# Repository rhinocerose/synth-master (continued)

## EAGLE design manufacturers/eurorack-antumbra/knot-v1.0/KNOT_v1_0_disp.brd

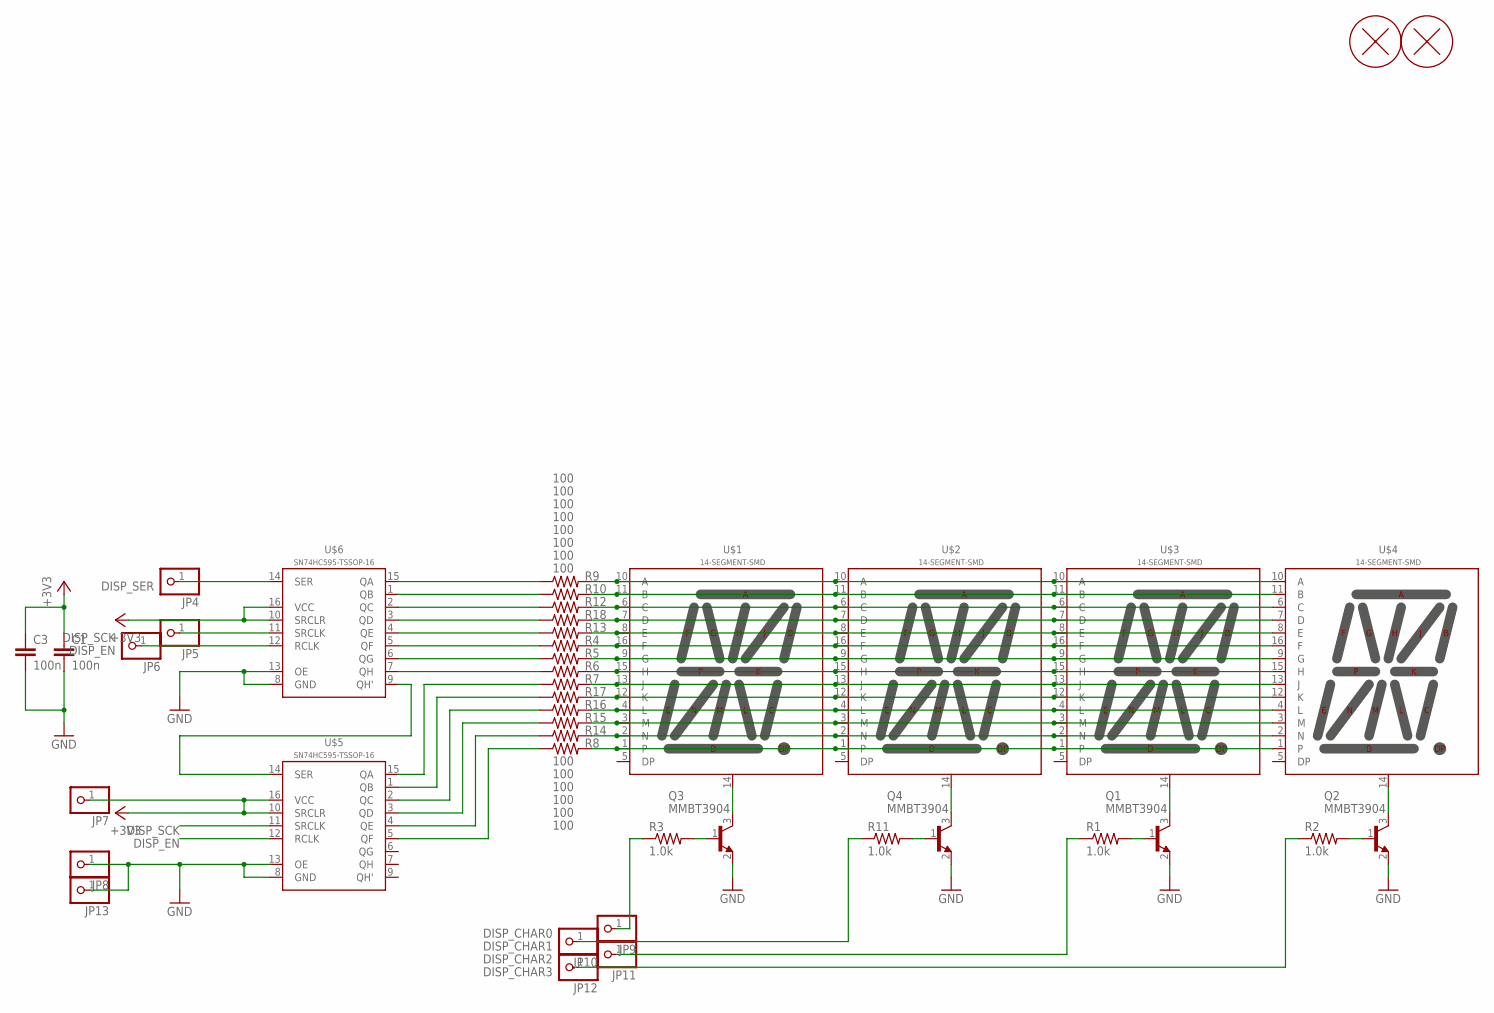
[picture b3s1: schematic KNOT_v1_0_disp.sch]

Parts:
C1, C3: 100n; RESISTOR_0603
H1, H2: PCB_SCREW
JP4, JP5, JP6, JP7, JP8, JP9, JP10, JP11, JP12, JP13: PINHD-1X1; 1X01
Q1, Q2, Q3, Q4: MMBT3904; SOT23
R1, R2, R3, R11: 1.0k; RESISTOR_0603
R4, R5, R6, R7, R8, R9, R10, R12, R13, R14, R15, R16, R17, R18: 100; RESISTOR_0603
U$1, U$2, U$3, U$4: 14-SEGMENT-SMD; 14-SEGMENT-0.4"-SMD
U$5, U$6: SN74HC595-TSSOP-16; TSSOP-16

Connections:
+3V3: C1.1, C3.1, JP7.1, U$5.10 (SRCLR), U$5.16 (VCC), U$6.10 (SRCLR), U$6.16 (VCC)
DISP_CHAR0: JP9.1, R3.1
DISP_CHAR1: JP10.1, R11.1
DISP_CHAR2: JP11.1, R1.1
DISP_CHAR3: JP12.1, R2.1
DISP_EN: JP6.1, U$5.12 (RCLK), U$6.12 (RCLK)
DISP_SCK: JP5.1, U$5.11 (SRCLK), U$6.11 (SRCLK)
DISP_SER: JP4.1, U$6.14 (SER)
GND: C1.2, C3.2, JP8.1, JP13.1, Q1.2 (E), Q2.2 (E), Q3.2 (E), Q4.2 (E), U$5.8 (GND), U$5.13 (OE), U$6.8 (GND), U$6.13 (OE)
unnamed: Q3.3 (C), U$1.14 (CATHODE)
unnamed: Q4.3 (C), U$2.14 (CATHODE)
unnamed: Q1.3 (C), U$3.14 (CATHODE)
unnamed: Q2.3 (C), U$4.14 (CATHODE)
unnamed: Q3.1 (B), R3.2
unnamed: Q4.1 (B), R11.2
unnamed: Q1.1 (B), R1.2
unnamed: Q2.1 (B), R2.2
unnamed: R9.2, U$1.10 (A), U$2.10 (A), U$3.10 (A), U$4.10 (A)
unnamed: R10.2, U$1.11 (B), U$2.11 (B), U$3.11 (B), U$4.11 (B)
unnamed: R12.2, U$1.6 (C), U$2.6 (C), U$3.6 (C), U$4.6 (C)
unnamed: R18.2, U$1.7 (D), U$2.7 (D), U$3.7 (D), U$4.7 (D)
unnamed: R13.2, U$1.8 (E), U$2.8 (E), U$3.8 (E), U$4.8 (E)
unnamed: R4.2, U$1.16 (F), U$2.16 (F), U$3.16 (F), U$4.16 (F)
unnamed: R5.2, U$1.9 (G), U$2.9 (G), U$3.9 (G), U$4.9 (G)
unnamed: R6.2, U$1.15 (H), U$2.15 (H), U$3.15 (H), U$4.15 (H)
unnamed: R7.2, U$1.13 (J), U$2.13 (J), U$3.13 (J), U$4.13 (J)
unnamed: R17.2, U$1.12 (K), U$2.12 (K), U$3.12 (K), U$4.12 (K)
unnamed: R16.2, U$1.4 (L), U$2.4 (L), U$3.4 (L), U$4.4 (L)
unnamed: R15.2, U$1.3 (M), U$2.3 (M), U$3.3 (M), U$4.3 (M)
unnamed: R14.2, U$1.2 (N), U$2.2 (N), U$3.2 (N), U$4.2 (N)
unnamed: R8.2, U$1.1, U$2.1, U$3.1, U$4.1
unnamed: R6.1, U$6.7 (QH)
unnamed: U$5.14 (SER), U$6.9 (QH')
unnamed: R9.1, U$6.15 (QA)
unnamed: R10.1, U$6.1 (QB)
unnamed: R12.1, U$6.2 (QC)
unnamed: R18.1, U$6.3 (QD)
unnamed: R13.1, U$6.4 (QE)
unnamed: R4.1, U$6.5 (QF)
unnamed: R5.1, U$6.6 (QG)
unnamed: R7.1, U$5.15 (QA)
unnamed: R17.1, U$5.1 (QB)
unnamed: R16.1, U$5.2 (QC)
unnamed: R15.1, U$5.3 (QD)
unnamed: R14.1, U$5.4 (QE)
unnamed: R8.1, U$5.5 (QF)

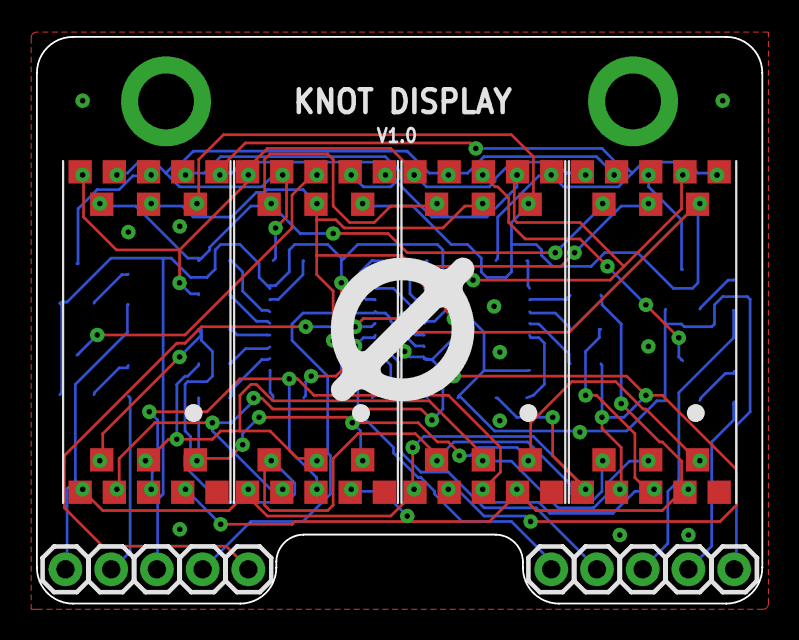
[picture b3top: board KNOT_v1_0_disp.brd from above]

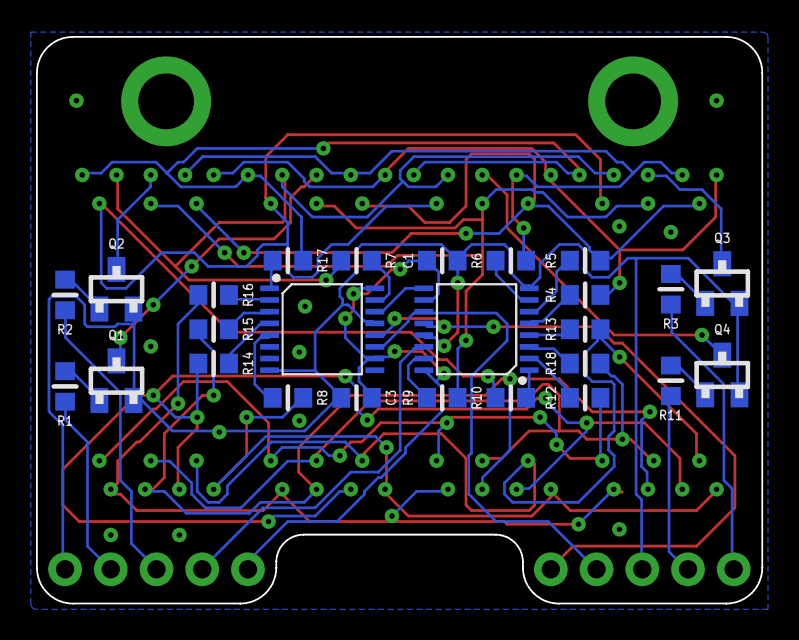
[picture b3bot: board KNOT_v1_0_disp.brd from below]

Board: 2 copper layers, 40.3 x 31.5 mm, 43 parts (26 on the bottom side), 46 nets.

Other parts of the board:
U$7: LOGO_8

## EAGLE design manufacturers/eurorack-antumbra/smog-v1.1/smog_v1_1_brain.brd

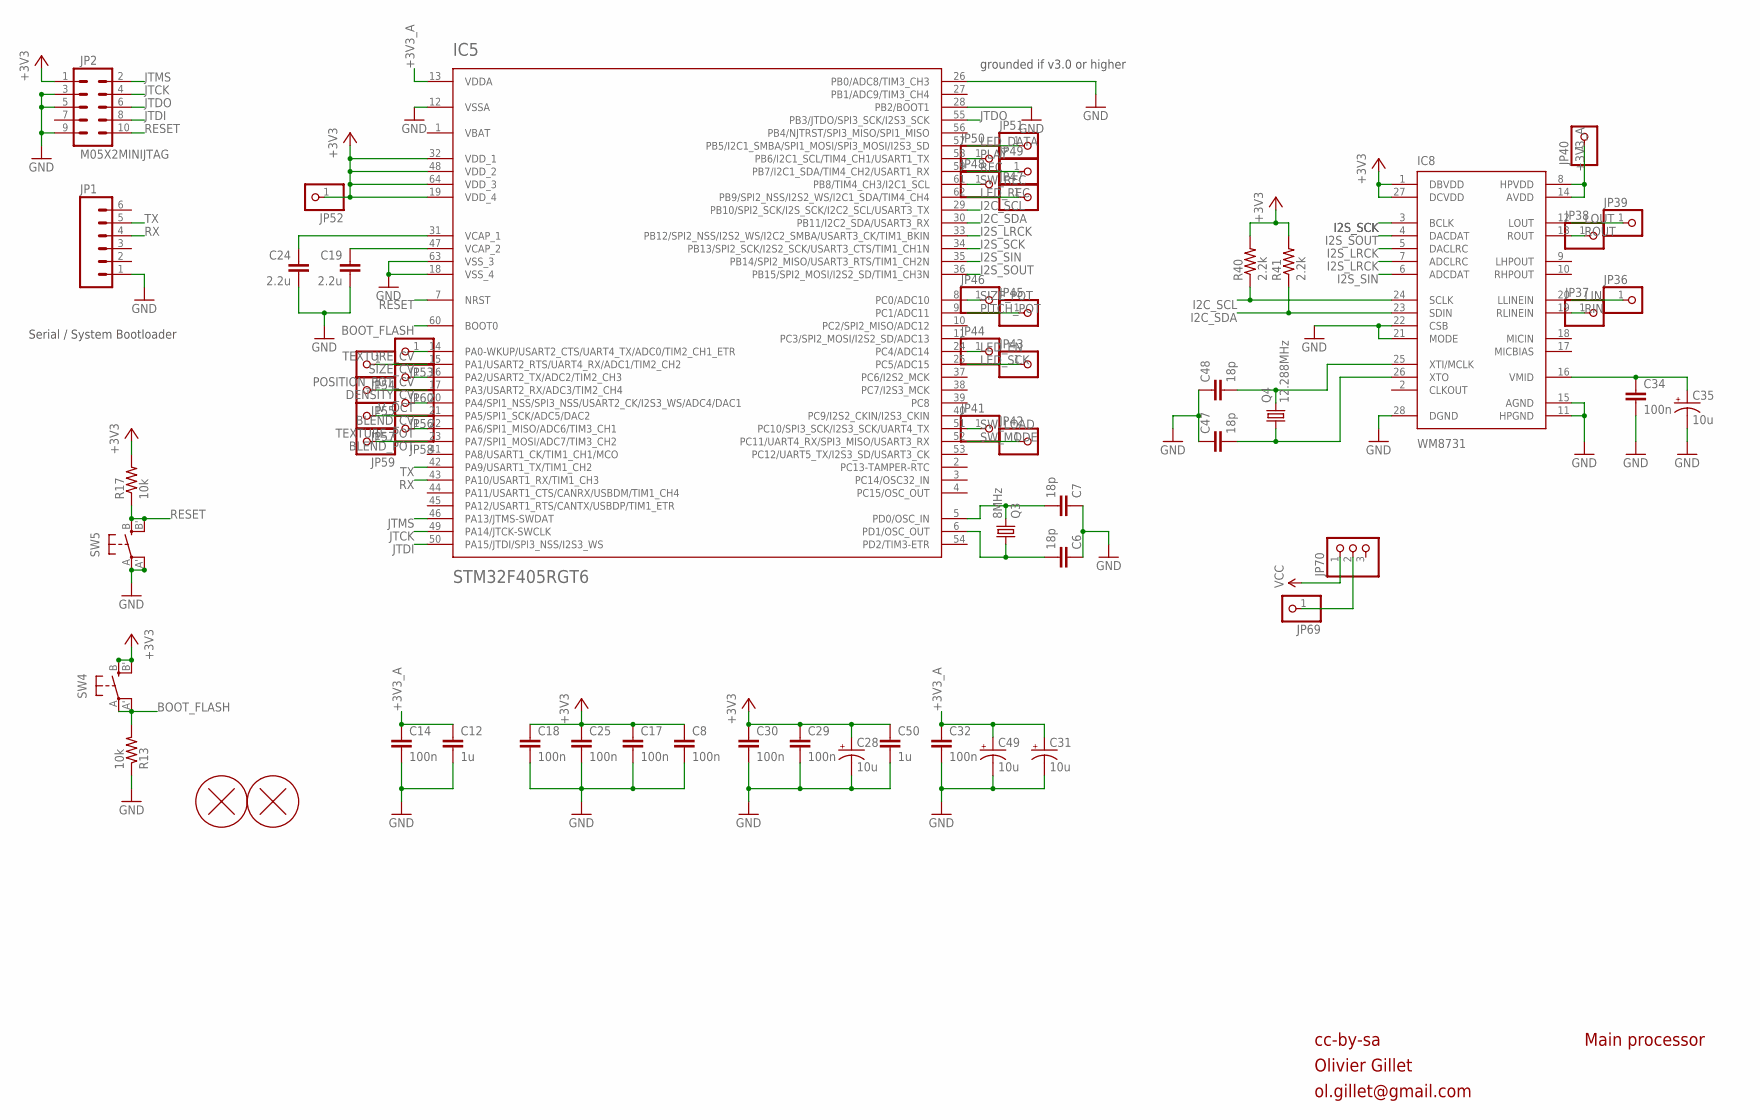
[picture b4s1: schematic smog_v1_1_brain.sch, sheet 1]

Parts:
C6, C7, C47, C48: 18p; RESISTOR_0603
C8, C14, C17, C18, C25, C29, C30, C32, C34: 100n; RESISTOR_0603
C12, C50: 1u; RESISTOR_0603
C19, C24: 2.2u; RESISTOR_0603
C28, C31, C35, C49: 10u; PANASONIC_B
H1, H2: PCB_SCREW
IC5: STM32F405RGT6; TQFP-10X10-64
IC8: WM8731; SSOP28
JP1: M06SIP; 1X06
JP2: M05X2MINIJTAG; 2X5-1.27
JP36, JP37, JP38, JP39, JP40, JP41, JP42, JP43, JP44, JP45, JP46, JP47, JP48, JP49, JP50, JP51, JP52, JP53, JP54, JP55, JP56, JP57, JP58, JP59, JP60, JP69: PINHD-1X1; 1X01
JP70: PINHD-1X3; 1X03
Q3: 8MHz; HC49UP
Q4: 12.288MHz; HC49UP
R13, R17: 10k; RESISTOR_0603
R40, R41: 2.2k; RESISTOR_0603
SW4, SW5: EVQQ2; EVQ-Q2

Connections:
+3V3: C8.1, C17.1, C18.1, C25.1, C28.+, C29.1, C30.1, C50.1, IC5.19 (VDD_4), IC5.32 (VDD_1), IC5.48 (VDD_2), IC5.64 (VDD_3), IC8.1 (DBVDD), IC8.27 (DCVDD), JP2.1, JP52.1, R17.2, R40.2, R41.2, SW4.B (S), SW4.B' (S1); also elsewhere on the board
+3V3_A: C12.1, C14.1, C31.+, C32.1, C49.+, IC5.13 (VDDA), IC8.8 (HPVDD), IC8.14 (AVDD), JP40.1; also elsewhere on the board
BLEND_CV: IC5.21 (PA5/SPI1_SCK/ADC5/DAC2), JP57.1
BLEND_POT: IC5.23 (PA7/SPI1_MOSI/ADC7/TIM3_CH2), JP59.1
BOOT_FLASH: IC5.60 (BOOT0), R13.2, SW4.A, SW4.A' (P1)
DENSITY_CV: IC5.17 (PA3/USART2_RX/ADC3/TIM2_CH4), JP55.1
GND: C6.1, C7.1, C8.2, C12.2, C14.2, C17.2, C18.2, C19.2, C24.2, C25.2, C28.-, C29.2, C30.2, C31.-, C32.2, C34.2, C35.-, C47.1, C48.1, C49.-, C50.2, IC5.12 (VSSA), IC5.18 (VSS_4), IC5.26 (PB0/ADC8/TIM3_CH3), IC5.28 (PB2/BOOT1), IC5.63 (VSS_3), IC8.11 (HPGND), IC8.15 (AGND), IC8.21 (MODE), IC8.22 (CSB), IC8.28 (DGND), JP1.1, JP2.3, JP2.5, JP2.9, R13.1, SW5.A, SW5.A' (P1); also elsewhere on the board
I2C_SCL: IC5.29 (PB10/SPI2_SCK/I2S_SCK/I2C2_SCL/USART3_TX), IC8.24 (SCLK), R40.1
I2C_SDA: IC5.30 (PB11/I2C2_SDA/USART3_RX), IC8.23 (SDIN), R41.1
I2S_LRCK: IC5.33 (PB12/SPI2_NSS/I2S2_WS/I2C2_SMBA/USART3_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), IC8.5 (DACLRC), IC8.7 (ADCLRC)
I2S_SCK: IC5.34 (PB13/SPI2_SCK/I2S2_SCK/USART3_CTS/TIM1_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), IC8.3 (BCLK)
I2S_SIN: IC5.35 (PB14/SPI2_MISO/USART3_RTS/TIM1_CH2N), IC8.6 (ADCDAT)
I2S_SOUT: IC5.36 (PB15/SPI2_MOSI/I2S2_SD/TIM1_CH3N), IC8.4 (DACDAT)
JTCK: IC5.49 (PA14/JTCK-SWCLK), JP2.4
JTDI: IC5.50 (PA15/JTDI/SPI3_NSS/I2S3_WS), JP2.8
JTDO: IC5.55 (PB3/JTDO/SPI3_SCK/I2S3_SCK), JP2.6
JTMS: IC5.46 (PA13/JTMS-SWDAT), JP2.2
LED_DATA: IC5.57 (PB5/I2C1_SMBA/SPI1_MOSI/SPI3_MOSI/I2S3_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), JP51.1
LED_EN: IC5.24 (PC4/ADC14), JP44.1
LED_REC: IC5.62 (PB9/SPI2_NSS/I2S2_WS/I2C1_SDA/TIM4_CH4), JP47.1
LED_SCK: IC5.25 (PC5/ADC15), JP43.1
LIN: IC8.20 (LLINEIN), JP36.1
LOUT: IC8.12 (LOUT), JP39.1
unnamed: C7.2, IC5.5 (PD0/OSC_IN), Q3.2
unnamed: C6.2, IC5.6 (PD1/OSC_OUT), Q3.1
unnamed: C19.1, IC5.47 (VCAP_2)
unnamed: C34.1, C35.+, IC8.16 (VMID)
unnamed: C24.1, IC5.31 (VCAP_1)
unnamed: C47.2, IC8.26 (XTO), Q4.1
unnamed: C48.2, IC8.25 (XTI/MCLK), Q4.2
unnamed: JP69.1, JP70.2
PITCH_POT: IC5.9 (PC1/ADC11), JP45.1
PLAY: IC5.58 (PB6/I2C1_SCL/TIM4_CH1/USART1_TX), JP50.1
POSITION_POT_CV: IC5.16 (PA2/USART2_TX/ADC2/TIM2_CH3), JP60.1
REC: IC5.59 (PB7/I2C1_SDA/TIM4_CH2/USART1_RX), JP49.1
RESET: IC5.7 (NRST), JP2.10, R17.1, SW5.B (S), SW5.B' (S1)
RIN: IC8.19 (RLINEIN), JP37.1
ROUT: IC8.13 (ROUT), JP38.1
RX: IC5.43 (PA10/USART1_RX/TIM1_CH3), JP1.4
SIZE_CV: IC5.15 (PA1/USART2_RTS/UART4_RX/ADC1/TIM2_CH2), JP54.1
SIZE_POT: IC5.8 (PC0/ADC10), JP46.1
SW_LOAD: IC5.51 (PC10/SPI3_SCK/I2S3_SCK/UART4_TX), JP41.1
SW_MODE: IC5.52 (PC11/UART4_RX/SPI3_MISO/USART3_RX), JP42.1
SW_REC: IC5.61 (PB8/TIM4_CH3/I2C1_SCL), JP48.1
TEXTURE_CV: IC5.14 (PA0-WKUP/USART2_CTS/UART4_TX/ADC0/TIM2_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), JP53.1
TEXTURE_POT: IC5.22 (PA6/SPI1_MISO/ADC6/TIM3_CH1), JP58.1
TX: IC5.42 (PA9/USART1_TX/TIM1_CH2), JP1.5
VBAT: IC5.1 (VBAT)
VCC: JP70.1; also elsewhere on the board
V_OCT: IC5.20 (PA4/SPI1_NSS/SPI3_NSS/USART2_CK/I2S3_WS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), JP56.1

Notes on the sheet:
cc-by-sa
Olivier Gillet
ol.gillet@gmail.com
Main processor
Serial / System Bootloader
grounded if v3.0 or higher

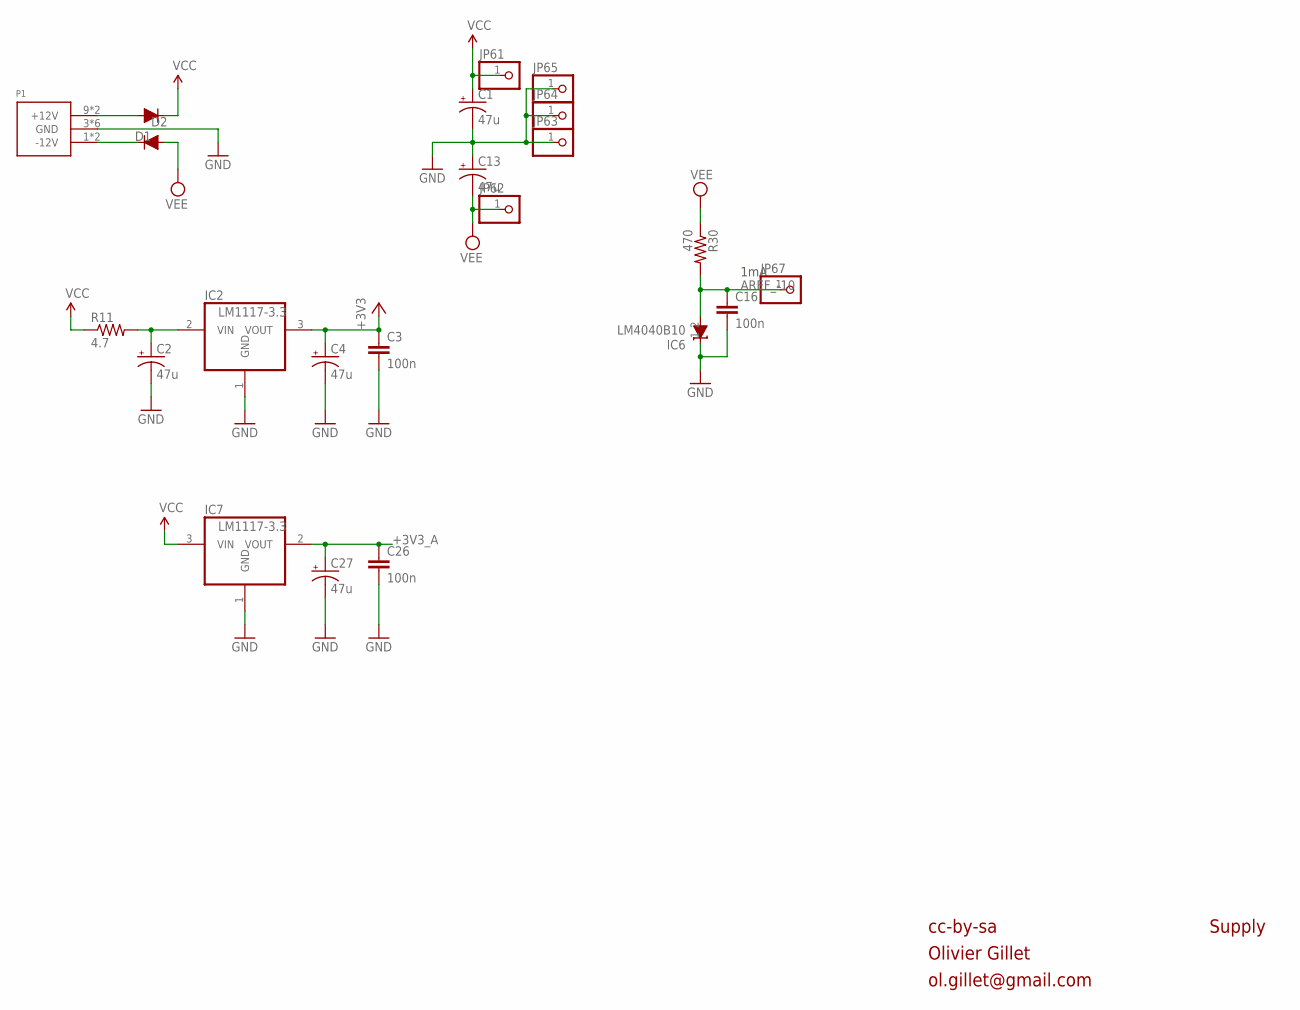
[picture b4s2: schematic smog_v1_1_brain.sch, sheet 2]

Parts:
C1, C2, C4, C13, C27: 47u; PANASONIC_D
C3, C16, C26: 100n; RESISTOR_0603
D1, D2: 1N5819HW; SOD123
IC2: LM1117-3.3; TO252
IC6: LM4040B10; SOT23
IC7: LM1117-3.3; SOT223
JP61, JP62, JP63, JP64, JP65, JP67: PINHD-1X1; 1X01
P1: POWER_SIMPLE10; POWER_10
R11: 4.7; RESISTOR_0603
R30: 470; RESISTOR_0603

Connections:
+3V3: C3.1, C4.+, IC2.3 (VOUT); also elsewhere on the board
+3V3_A: C26.1, C27.+, IC7.2 (VOUT); also elsewhere on the board
AREF_-10: C16.1, IC6.2 (A), JP67.1, R30.2
GND: C1.-, C2.-, C3.2, C4.-, C13.+, C16.2, C26.2, C27.-, IC2.1 (GND), IC6.1 (C), IC7.1 (GND), JP63.1, JP64.1, JP65.1, P1.3 (GND), P1.4 (GND), P1.5 (GND), P1.6 (GND), P1.7 (GND), P1.8 (GND); also elsewhere on the board
unnamed: D1.+, P1.9 (+12V), P1.10 (+12V)
unnamed: D2.-, P1.1 (-12V), P1.2 (-12V)
unnamed: C2.+, IC2.2 (VIN), R11.2
VCC: C1.+, D1.-, IC7.3 (VIN), JP61.1, R11.1; also elsewhere on the board
VEE: C13.-, D2.+, JP62.1, R30.1

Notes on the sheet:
1mA
cc-by-sa
Olivier Gillet
ol.gillet@gmail.com
Supply

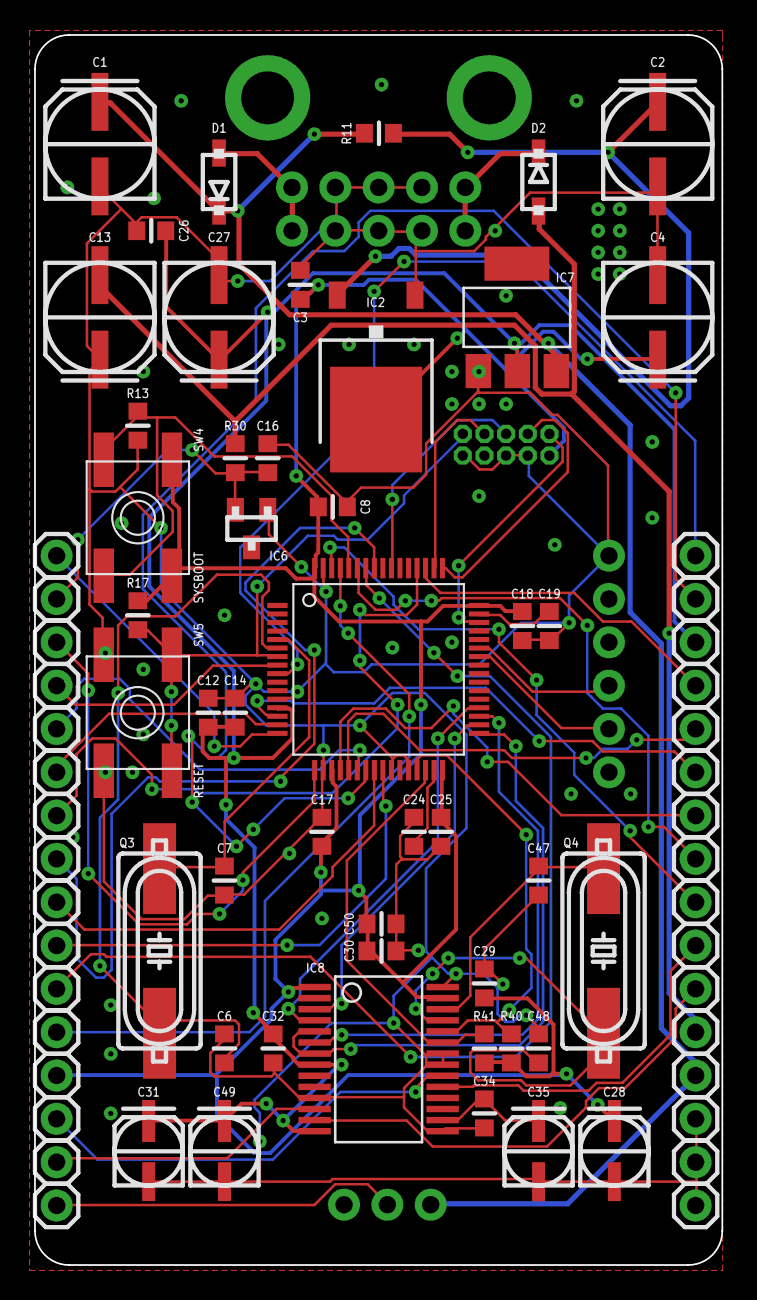
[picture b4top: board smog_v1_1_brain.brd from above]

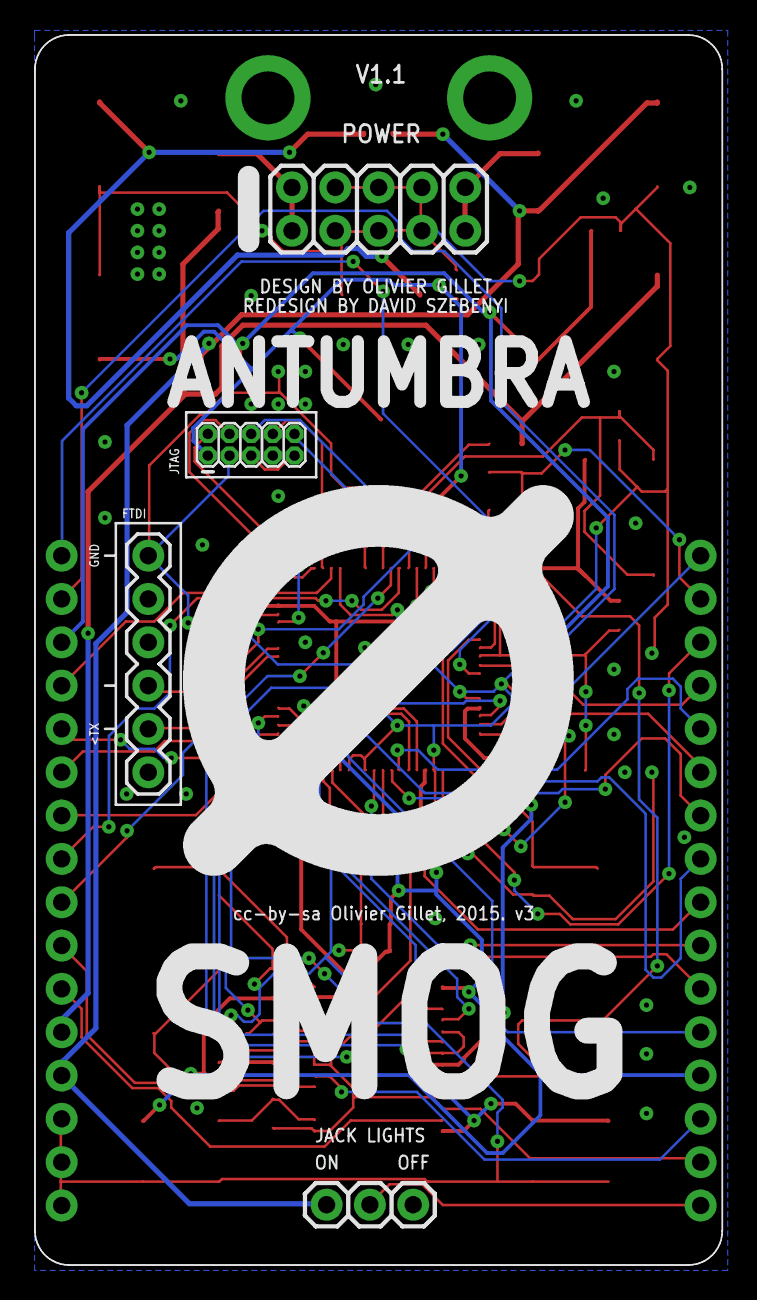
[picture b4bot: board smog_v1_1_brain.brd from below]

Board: 2 copper layers, 40.3 x 72.1 mm, 85 parts (5 on the bottom side), 54 nets.

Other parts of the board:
U$1: LOGO_23

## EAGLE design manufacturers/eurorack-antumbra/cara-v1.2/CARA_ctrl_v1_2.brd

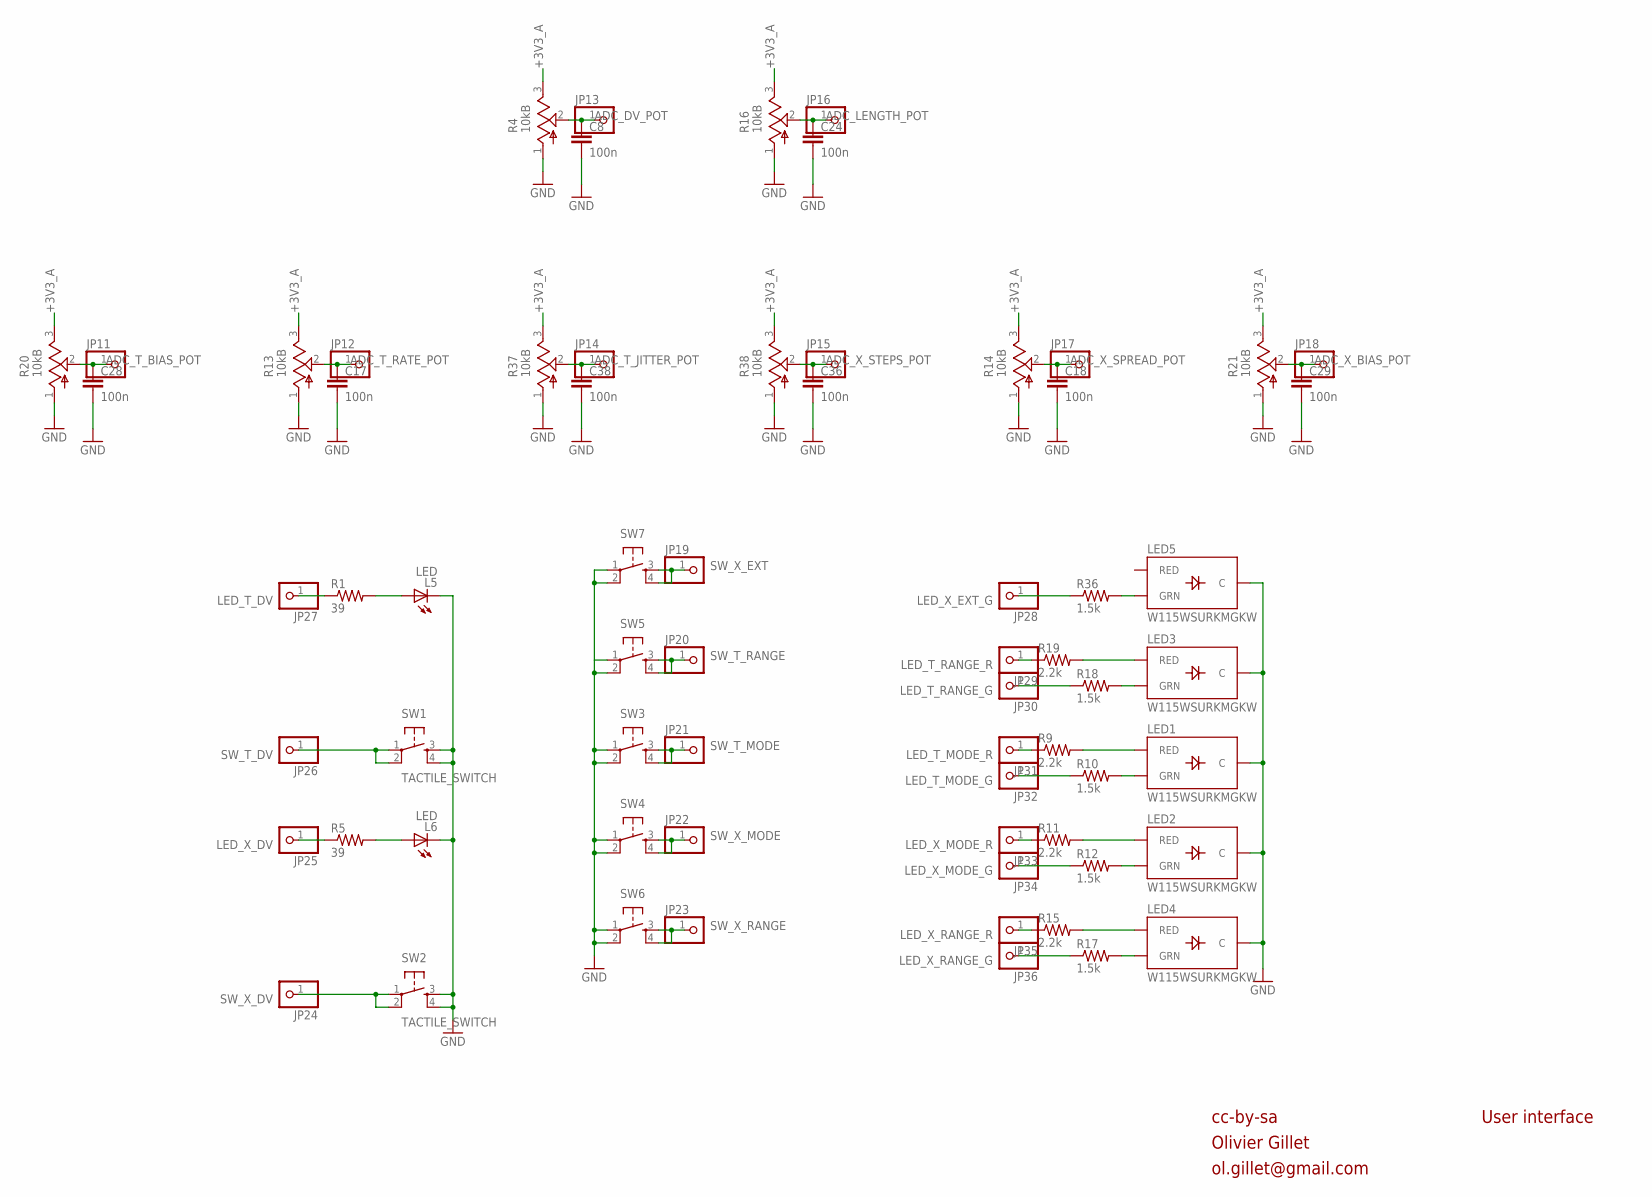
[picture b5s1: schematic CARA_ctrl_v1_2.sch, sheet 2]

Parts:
C8, C17, C18, C24, C28, C29, C36, C38: 100n; RESISTOR_0603
JP11, JP12, JP13, JP14, JP15, JP16, JP17, JP18, JP19, JP20, JP21, JP22, JP23, JP24, JP25, JP26, JP27, JP28, JP29, JP30, JP31, JP32, JP33, JP34, JP35, JP36: PINHD-1X1; 1X01
L5, L6: LED; LED_3MM
LED1, LED2, LED3, LED4, LED5: W115WSURKMGKW; LED_BICOLOR
R1, R5: 39; RESISTOR_0603
R4, R13, R14, R16, R20, R21, R37, R38: 10kB; ALPS_POT_VERTICAL
R9, R11, R15, R19: 2.2k; RESISTOR_0603
R10, R12, R17, R18, R36: 1.5k; RESISTOR_0603
SW1, SW2, SW3, SW4, SW5, SW6, SW7: TACTILE_SWITCH; TACTILE-PTH

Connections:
+3V3_A: R4.3 (B), R13.3 (B), R14.3 (B), R16.3 (B), R20.3 (B), R21.3 (B), R37.3 (B), R38.3 (B); also elsewhere on the board
ADC_DV_POT: C8.1, JP13.1, R4.2 (W)
ADC_LENGTH_POT: C24.1, JP16.1, R16.2 (W)
ADC_T_BIAS_POT: C28.1, JP11.1, R20.2 (W)
ADC_T_JITTER_POT: C38.1, JP14.1, R37.2 (W)
ADC_T_RATE_POT: C17.1, JP12.1, R13.2 (W)
ADC_X_BIAS_POT: C29.1, JP18.1, R21.2 (W)
ADC_X_SPREAD_POT: C18.1, JP17.1, R14.2 (W)
ADC_X_STEPS_POT: C36.1, JP15.1, R38.2 (W)
GND: C8.2, C17.2, C18.2, C24.2, C28.2, C29.2, C36.2, C38.2, L5.K (C), L6.K (C), LED1.2 (C), LED2.2 (C), LED3.2 (C), LED4.2 (C), LED5.2 (C), R4.1 (A), R13.1 (A), R14.1 (A), R16.1 (A), R20.1 (A), R21.1 (A), R37.1 (A), R38.1 (A), SW1.3, SW1.4, SW2.3, SW2.4, SW3.1, SW3.2, SW4.1, SW4.2, SW5.1, SW5.2, SW6.1, SW6.2, SW7.1, SW7.2; also elsewhere on the board
LED_T_DV: JP27.1, R1.1
LED_T_MODE_G: JP32.1, R10.1
LED_T_MODE_R: JP31.1, R9.1
LED_T_RANGE_G: JP30.1, R18.1
LED_T_RANGE_R: JP29.1, R19.1
LED_X_DV: JP25.1, R5.1
LED_X_EXT_G: JP28.1, R36.1
LED_X_MODE_G: JP34.1, R12.1
LED_X_MODE_R: JP33.1, R11.1
LED_X_RANGE_G: JP36.1, R17.1
LED_X_RANGE_R: JP35.1, R15.1
unnamed: L5.A, R1.2
unnamed: L6.A, R5.2
unnamed: LED3.3 (RED), R19.2
unnamed: LED3.1 (GRN), R18.2
unnamed: LED1.3 (RED), R9.2
unnamed: LED2.3 (RED), R11.2
unnamed: LED2.1 (GRN), R12.2
unnamed: LED4.3 (RED), R15.2
unnamed: LED1.1 (GRN), R10.2
unnamed: LED4.1 (GRN), R17.2
unnamed: LED5.1 (GRN), R36.2
SW_T_DV: JP26.1, SW1.1, SW1.2
SW_T_MODE: JP21.1, SW3.3, SW3.4
SW_T_RANGE: JP20.1, SW5.3, SW5.4
SW_X_DV: JP24.1, SW2.1, SW2.2
SW_X_EXT: JP19.1, SW7.3, SW7.4
SW_X_MODE: JP22.1, SW4.3, SW4.4
SW_X_RANGE: JP23.1, SW6.3, SW6.4

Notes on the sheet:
cc-by-sa
Olivier Gillet
ol.gillet@gmail.com
User interface

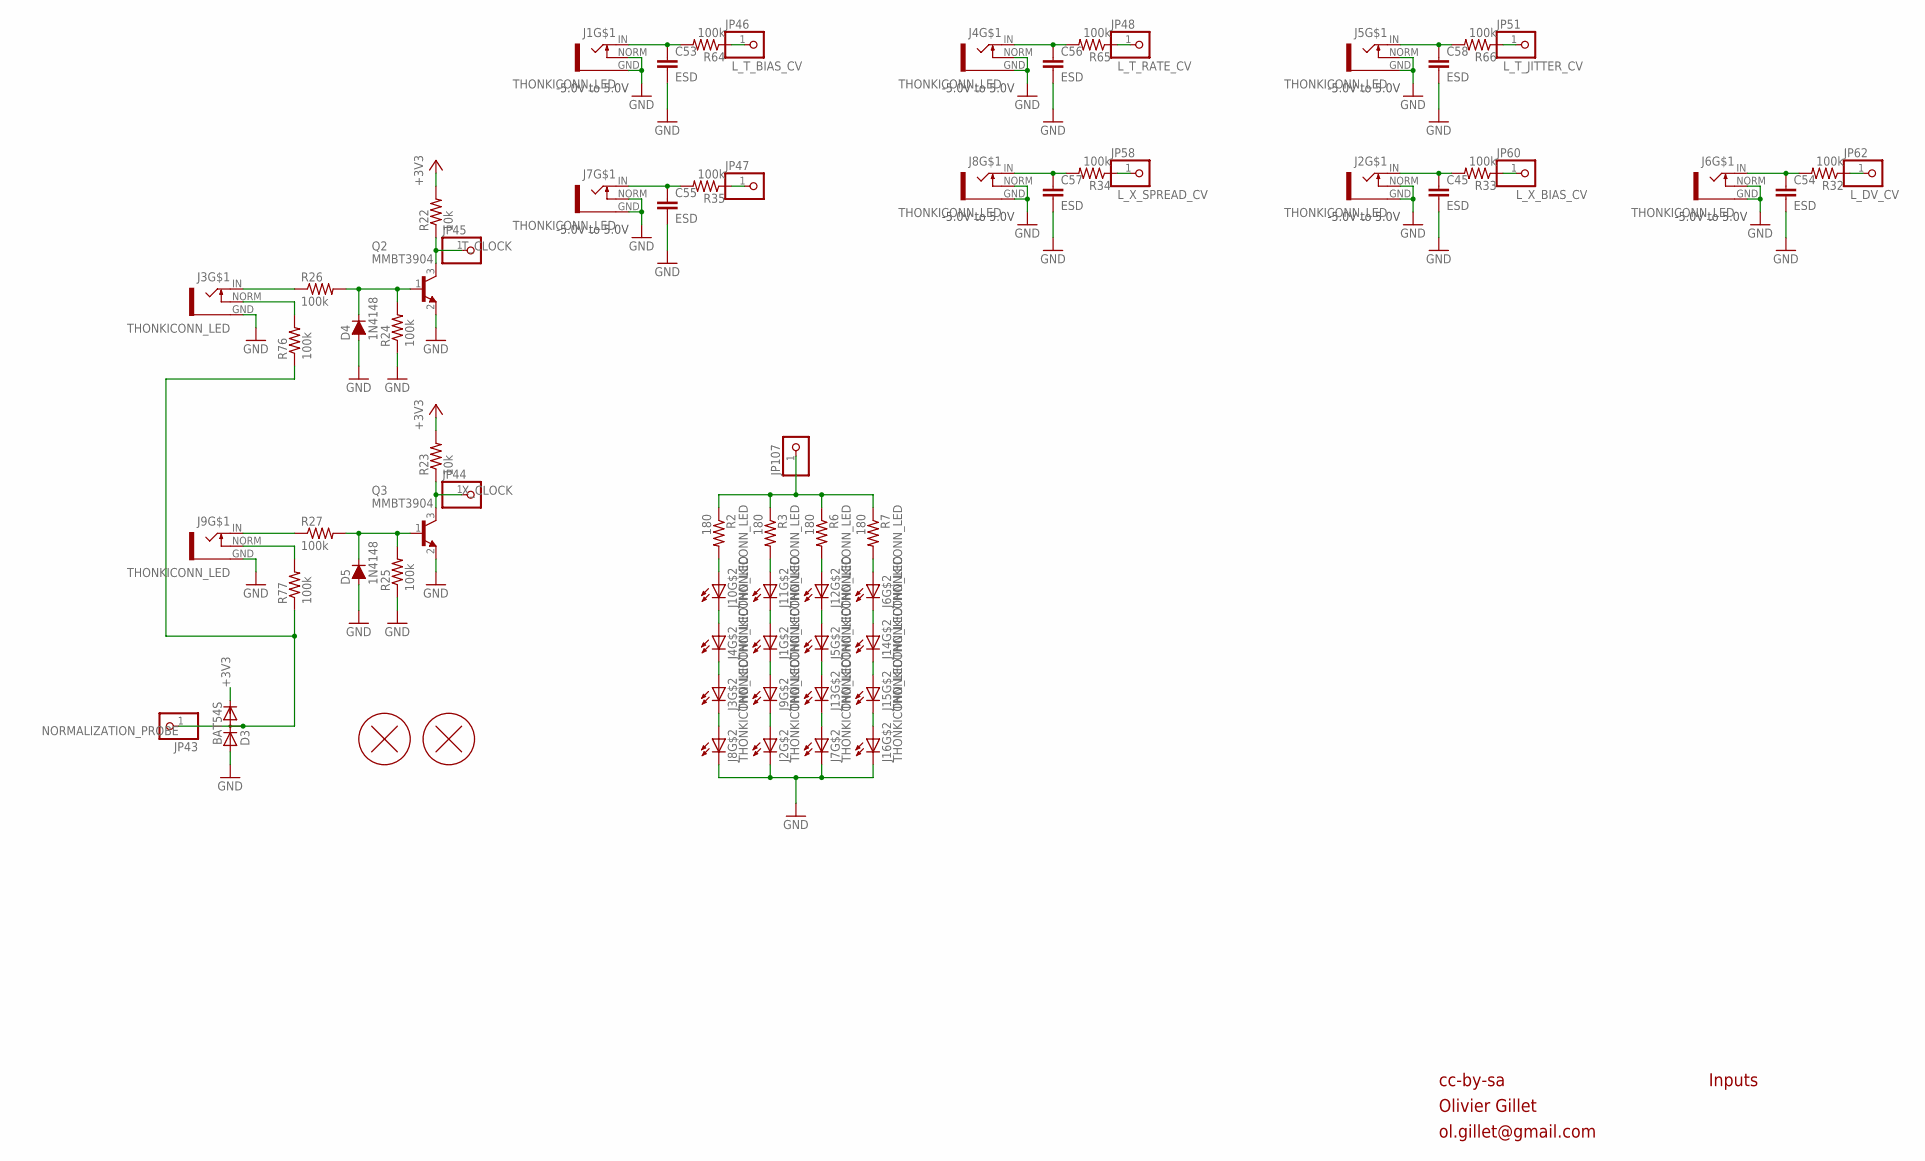
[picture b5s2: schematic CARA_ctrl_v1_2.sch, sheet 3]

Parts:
C45, C53, C54, C55, C56, C57, C58: ESD; RESISTOR_0603
D3: BAT54S; SOT23
D4, D5: 1N4148; SOD123
H1, H2: PCB_SCREW
J1, J2, J3, J4, J5, J6, J7, J8, J9, J10, J11, J12, J13, J14, J15, J16: THONKICONN_LED; LED_JACK
JP43, JP44, JP45, JP46, JP47, JP48, JP51, JP58, JP60, JP62, JP107: PINHD-1X1; 1X01
Q2, Q3: MMBT3904; SOT23
R2, R3, R6, R7: 180; RESISTOR_0603
R22, R23: 10k; RESISTOR_0603
R24, R25, R26, R27, R32, R33, R34, R35, R64, R65, R66, R76, R77: 100k; RESISTOR_0603

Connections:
+3V3: D3.2 (C), R22.2, R23.2; also elsewhere on the board
GND: C45.2, C53.2, C54.2, C55.2, C56.2, C57.2, C58.2, D3.1 (A), D4.+, D5.+, J1.GND, J1.NORM, J2.C, J2.GND, J2.NORM, J3.GND, J4.GND, J4.NORM, J5.GND, J5.NORM, J6.GND, J6.NORM, J7.C, J7.GND, J7.NORM, J8.C, J8.GND, J8.NORM, J9.GND, J16.C, Q2.2 (E), Q3.2 (E), R24.1, R25.1; also elsewhere on the board
L_DV_CV: JP62.1, R32.1
L_T_BIAS_CV: JP46.1, R64.1
L_T_JITTER_CV: JP51.1, R66.1
L_T_RATE_CV: JP48.1, R65.1
L_X_BIAS_CV: JP60.1, R33.1
L_X_SPREAD_CV: JP58.1, R34.1
L_X_STEPS_CV: JP47.1, R35.1
MORPH_IN: C53.1, J1.IN, R64.2
MORPH_IN1: C55.1, J7.IN, R35.2
MORPH_IN3: C56.1, J4.IN, R65.2
MORPH_IN4: C57.1, J8.IN, R34.2
MORPH_IN5: C54.1, J6.IN, R32.2
MORPH_IN6: C58.1, J5.IN, R66.2
MORPH_IN7: C45.1, J2.IN, R33.2
unnamed: J4.A, J10.C
unnamed: J3.A, J4.C
unnamed: J1.A, J11.C
unnamed: J1.C, J9.A
unnamed: J3.C, J8.A
unnamed: J5.A, J12.C
unnamed: J6.C, J14.A
unnamed: J2.A, J9.C
unnamed: J5.C, J13.A
unnamed: J7.A, J13.C
unnamed: J14.C, J15.A
unnamed: J15.C, J16.A
unnamed: J10.A, R2.2
unnamed: J12.A, R6.2
unnamed: J6.A, R7.2
unnamed: J11.A, R3.2
unnamed: J9.IN, R27.1
unnamed: JP107.1, R2.1, R3.1, R6.1, R7.1
unnamed: J9.NORM, R77.2
unnamed: J3.NORM, R76.2
unnamed: D4.-, Q2.1 (B), R24.2, R26.2
unnamed: D5.-, Q3.1 (B), R25.2, R27.2
unnamed: J3.IN, R26.1
NORMALIZATION_PROBE: D3.3 (AC), JP43.1, R76.1, R77.1
T_CLOCK: JP45.1, Q2.3 (C), R22.1
X_CLOCK: JP44.1, Q3.3 (C), R23.1

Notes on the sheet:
cc-by-sa
Olivier Gillet
ol.gillet@gmail.com
Inputs
-5.0V to 5.0V
